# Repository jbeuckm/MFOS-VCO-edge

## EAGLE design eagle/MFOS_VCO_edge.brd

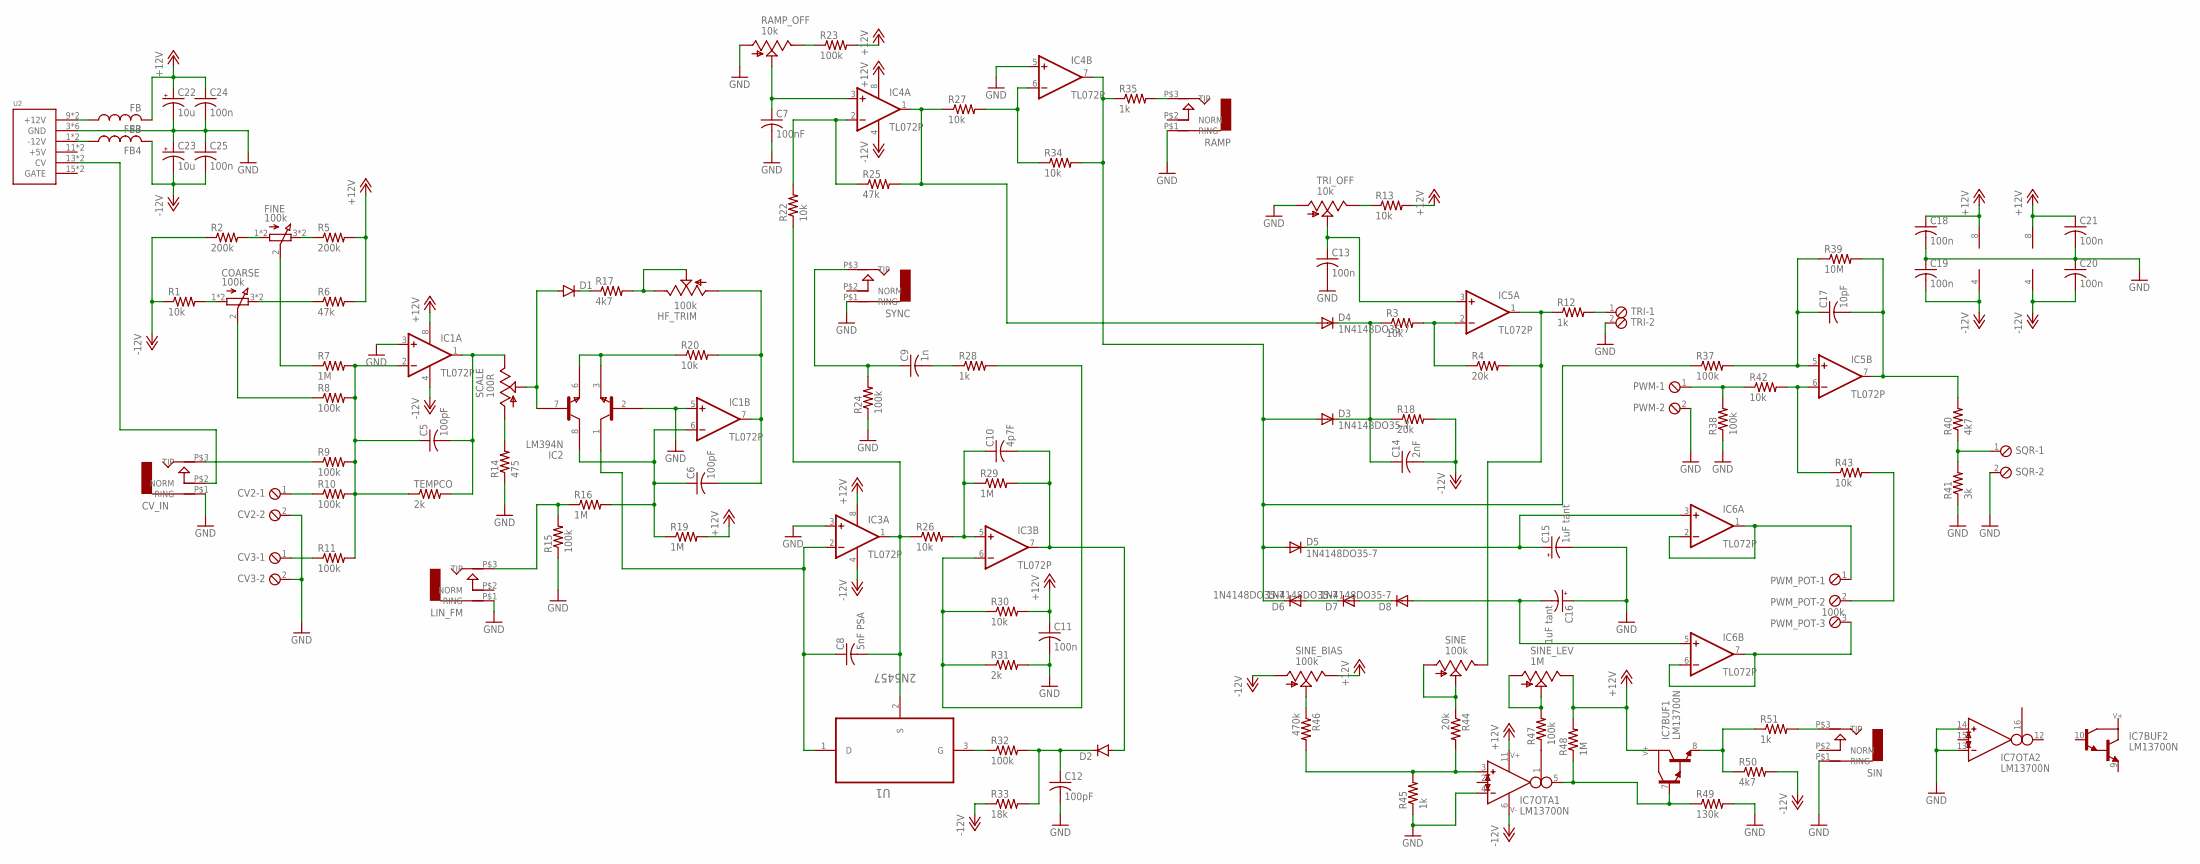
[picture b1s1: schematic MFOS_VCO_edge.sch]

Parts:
C5, C6, C12: 100pF; C050-024X044
C7: 100nF; C050-024X044
C8: 5nF PSA; C050-024X044
C9: 1n; C050-024X044
C10: 4p7F; C050-024X044
C11, C24, C25: 100n; C050-024X044
C13: 100n; C050-030X075
C14: 2nF; C050-030X075
C15, C16: 1uF tant; B45181A
C17: 10pF; C050-024X044
C18, C19, C20, C21: 100n; C1206
C22, C23: 10u; B45181A
COARSE: 100k; 3RP/1610N
CV2, CV3: MPT2; 2POL254
CV_IN: AUDIO-JACKITEAD; JACK-90DEG-ITEAD
D1, D2: DIODE1N4148; DIODE-1N4148
D3, D4, D5, D6, D7, D8: 1N4148DO35-7; DO35-7
FB3, FB4: FB
FINE: 100k; 3RP/1610N
HF_TRIM: 100k; B64W
IC1, IC3, IC4, IC5, IC6: TL072P; DIL08
IC2: LM394N; DIL08
IC7: LM13700N; DIL16
LIN_FM: AUDIO-JACKITEAD; JACK-90DEG-ITEAD
PWM: MPT2; 2POL254
PWM_POT: 100k; 3POL254
R1, R3, R13, R20, R22, R26, R27, R30, R34, R42, R43: 10k; 0207/7
R2, R5: 200k; 0207/7
R4, R18, R44: 20k; 0207/7
R6, R25: 47k; 0207/7
R7, R16, R19, R29, R48: 1M; 0207/7
R8, R9, R10, R11, R15, R23, R24, R32, R37, R38, R47: 100k; 0207/7
R12, R28, R35, R45, R51: 1k; 0207/7
R14: 475; 0207/7
R17, R40, R50: 4k7; 0207/7
R31: 2k; 0207/7
R33: 18k; 0207/7
R39: 10M; 0207/7
R41: 3k; 0207/7
R46: 470k; 0207/7
R49: 130k; 0207/7
RAMP: AUDIO-JACKITEAD; JACK-90DEG-ITEAD
RAMP_OFF: 10k; B64W
SCALE: 100R; B64W
SIN: AUDIO-JACKITEAD; JACK-90DEG-ITEAD
SINE: 100k; B64W
SINE_BIAS: 100k; B64W
SINE_LEV: 1M; B64W
SQR: MPT2; 2POL254
SYNC: AUDIO-JACKITEAD; JACK-90DEG-ITEAD
TEMPCO: 2k; 0207/2V
TRI: MPT2; 2POL254
TRI_OFF: 10k; B64W
U1: 2N5457; TO127P254X732-3
U2: POWER; POWER_16

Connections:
+12V: C11.1, C18.1, C21.1, C22.+, C24.1, FB3.P$2 (2), IC1.8 (V+), IC3.8 (V+), IC4.8 (V+), IC5.8 (V+), IC6.8 (V+), IC7.11 (V+), R5.2, R6.2, R13.2, R19.2, R23.2, R30.2, R48.2, SINE_BIAS.E, SINE_LEV.E
-12V: C14.2, C19.2, C20.2, C23.-, C25.2, FB4.P$2 (2), IC1.4 (V-), IC3.4 (V-), IC4.4 (V-), IC5.4 (V-), IC6.4 (V-), IC7.6 (V-), R1.1, R2.1, R18.2, R33.1, R50.2, SINE_BIAS.A
GND: C7.2, C11.2, C12.2, C13.2, C15.-, C16.+, C18.2, C19.1, C20.1, C21.2, C22.-, C23.+, C24.2, C25.1, CV2.2, CV3.2, CV_IN.P$1 (RING), IC1.3 (+IN), IC1.5 (+IN), IC2.2 (B1), IC3.3 (+IN), IC4.5 (+IN), IC7.4 (IN_N), IC7.13 (IN_N), IC7.14 (IN_P), LIN_FM.P$1 (RING), PWM.2, R14.1, R15.1, R24.1, R31.2, R38.1, R41.1, R45.1, R49.2, RAMP.P$1 (RING), RAMP_OFF.A, SIN.P$1 (RING), SQR.2, SYNC.P$1 (RING), TRI.2, TRI_OFF.A, U2.3 (GND), U2.4 (GND), U2.5 (GND), U2.6 (GND), U2.7 (GND), U2.8 (GND)
unnamed: COARSE.1 (A), COARSE.4 (A), R1.2
unnamed: FINE.1 (A), FINE.4 (A), R2.2
unnamed: FINE.3 (E), FINE.6 (E), R5.1
unnamed: COARSE.3 (E), COARSE.6 (E), R6.1
unnamed: FINE.2 (S), R7.1
unnamed: COARSE.2 (S), R8.1
unnamed: R14.2, SCALE.A
unnamed: D1.A, IC2.7 (B2), SCALE.P$1 (S), SCALE.S
unnamed: C5.2, IC1.1 (OUT), SCALE.E, TEMPCO.2
unnamed: C5.1, IC1.2 (-IN), R7.2, R8.2, R9.2, R10.2, R11.2, TEMPCO.1
unnamed: IC2.3 (E1), IC2.6 (E2), R20.1
unnamed: CV_IN.P$2 (NORM), U2.13 (CV), U2.14 (CV)
unnamed: HF_TRIM.E, HF_TRIM.P$1 (S), HF_TRIM.S, R17.2
unnamed: D1.C, R17.1
unnamed: C6.2, HF_TRIM.A, IC1.7 (OUT), R20.2
unnamed: CV_IN.P$3 (TIP), R9.1
unnamed: CV2.1, R10.1
unnamed: CV3.1, R11.1
unnamed: LIN_FM.P$3 (TIP), R15.2, R16.1
unnamed: C8.2, IC3.1 (OUT), R22.1, R26.1, U1.2 (S)
unnamed: C10.1, IC3.5 (+IN), R26.2, R29.1
unnamed: C8.1, IC2.1 (C1), IC3.2 (-IN), U1.1 (D)
unnamed: C9.2, R28.1
unnamed: C9.1, R24.2, SYNC.P$3 (TIP)
unnamed: IC3.6 (-IN), R28.2, R30.1, R31.1
unnamed: R23.1, RAMP_OFF.E
unnamed: C7.1, IC4.3 (+IN), RAMP_OFF.P$1 (S), RAMP_OFF.S
unnamed: R32.1, U1.3 (G)
unnamed: C10.2, D2.A, IC3.7 (OUT), R29.2
unnamed: IC4.2 (-IN), R22.2, R25.1
unnamed: C12.1, D2.C, R32.2, R33.2
unnamed: D4.A, IC4.1 (OUT), R25.2, R27.1
unnamed: IC4.6 (-IN), R27.2, R34.1
unnamed: D3.A, D5.A, D6.C, IC4.7 (OUT), R34.2, R35.1, R37.1
unnamed: R35.2, RAMP.P$3 (TIP)
unnamed: C6.1, IC1.6 (-IN), IC2.8 (C2), R16.2, R19.1
unnamed: FB3.P$1 (1), U2.9 (+12V), U2.10 (+12V)
unnamed: D6.A, D7.C
unnamed: D7.A, D8.C
unnamed: C14.1, D3.C, D4.C, R3.1, R18.1
unnamed: IC5.2 (-IN), R3.2, R4.1
unnamed: IC5.1 (OUT), R4.2, R12.1, SINE.E
unnamed: R12.2, TRI.1
unnamed: R13.1, TRI_OFF.E
unnamed: C13.1, IC5.3 (+IN), TRI_OFF.P$1 (S), TRI_OFF.S
unnamed: C16.-, D8.A, IC6.5 (+IN)
unnamed: C15.+, D5.C, IC6.3 (+IN)
unnamed: IC6.1 (OUT), IC6.2 (-IN), PWM_POT.1
unnamed: IC6.6 (-IN), IC6.7 (OUT), PWM_POT.3
unnamed: PWM.1, R38.2, R42.1
unnamed: C17.1, IC5.5 (+IN), R37.2, R39.1
unnamed: C17.2, IC5.7 (OUT), R39.2, R40.2
unnamed: R40.1, R41.2, SQR.1
unnamed: IC5.6 (-IN), R42.2, R43.1
unnamed: PWM_POT.2, R43.2
unnamed: R44.1, SINE.A, SINE.P$1 (S), SINE.S
unnamed: IC7.3 (IN_P), R44.2, R45.2, R46.2
unnamed: R46.1, SINE_BIAS.P$1 (S), SINE_BIAS.S
unnamed: IC7.1 (I_BIAS), R47.1
unnamed: R47.2, SINE_LEV.A, SINE_LEV.P$1 (S), SINE_LEV.S
unnamed: IC7.5 (OUT), IC7.7 (B), R48.1, R49.1
unnamed: R51.2, SIN.P$3 (TIP)
unnamed: IC7.8 (E), R50.1, R51.1
unnamed: FB4.P$1 (1), U2.1 (-12V), U2.2 (-12V)

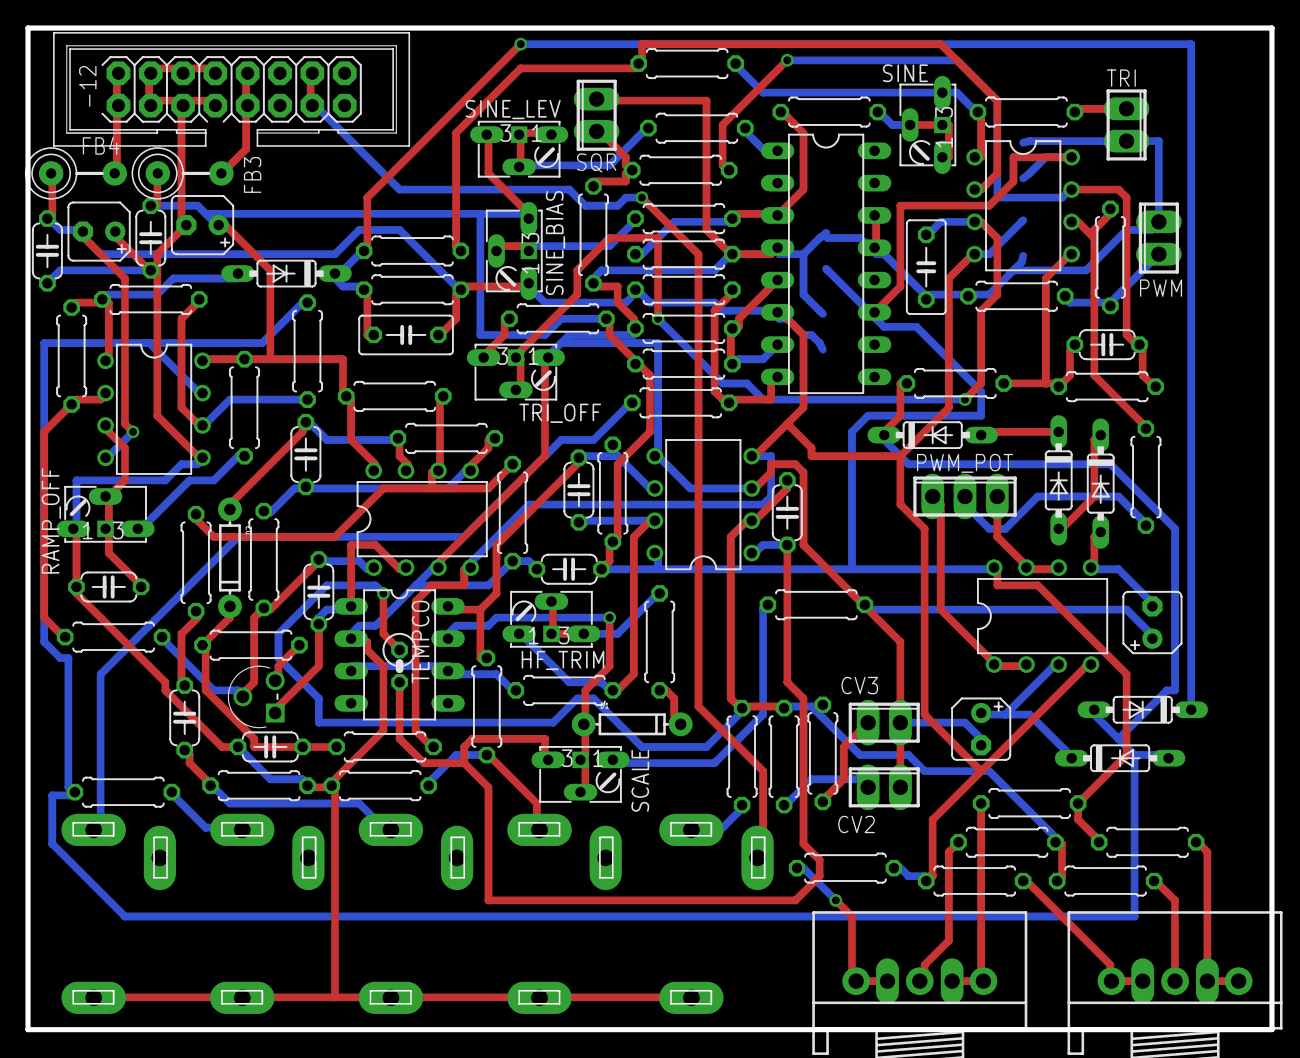
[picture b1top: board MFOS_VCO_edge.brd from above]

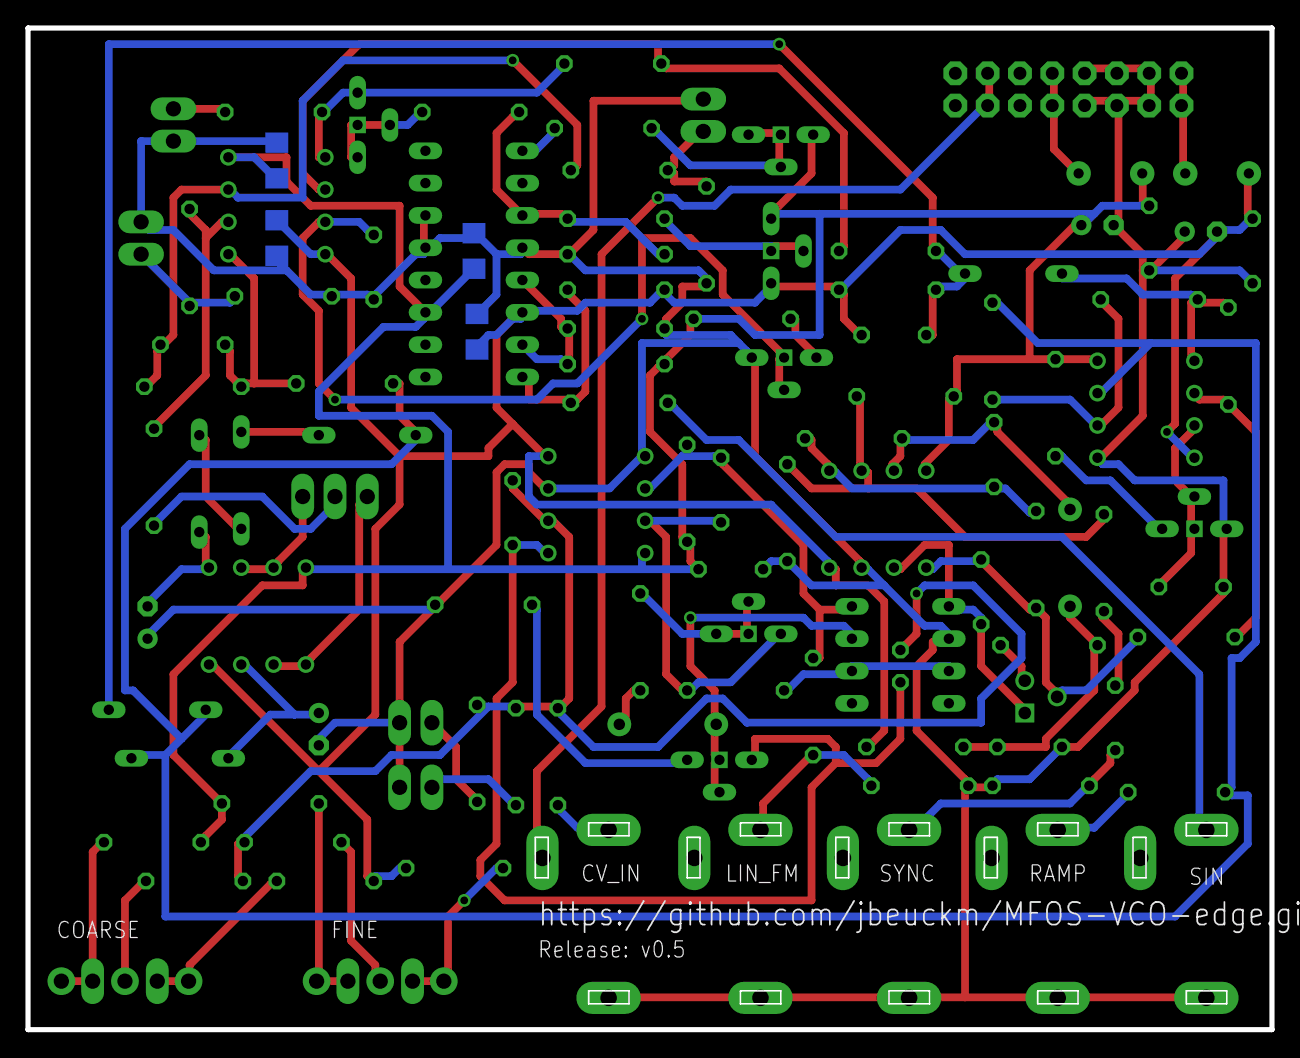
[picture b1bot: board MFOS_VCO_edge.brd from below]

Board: 2 copper layers, 97.8 x 78.7 mm, 110 parts (4 on the bottom side), 67 nets.

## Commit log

2017-09-03 flexible trimmers and grounded air outputs and connector for PWM pot
2017-09-03 slightly narrower
2017-09-03 added board link and version
2017-09-19 jack labels onto the back
2017-09-19 fixed one label
2017-09-24 tweaked cv input labels
2017-12-16 working panel

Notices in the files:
parts and their libraries:
SparkFun-DiscreteSemi: Licensing: Creative Commons ShareAlike 4.0 International - https://creativecommons.org/licenses/by-sa/4.0
